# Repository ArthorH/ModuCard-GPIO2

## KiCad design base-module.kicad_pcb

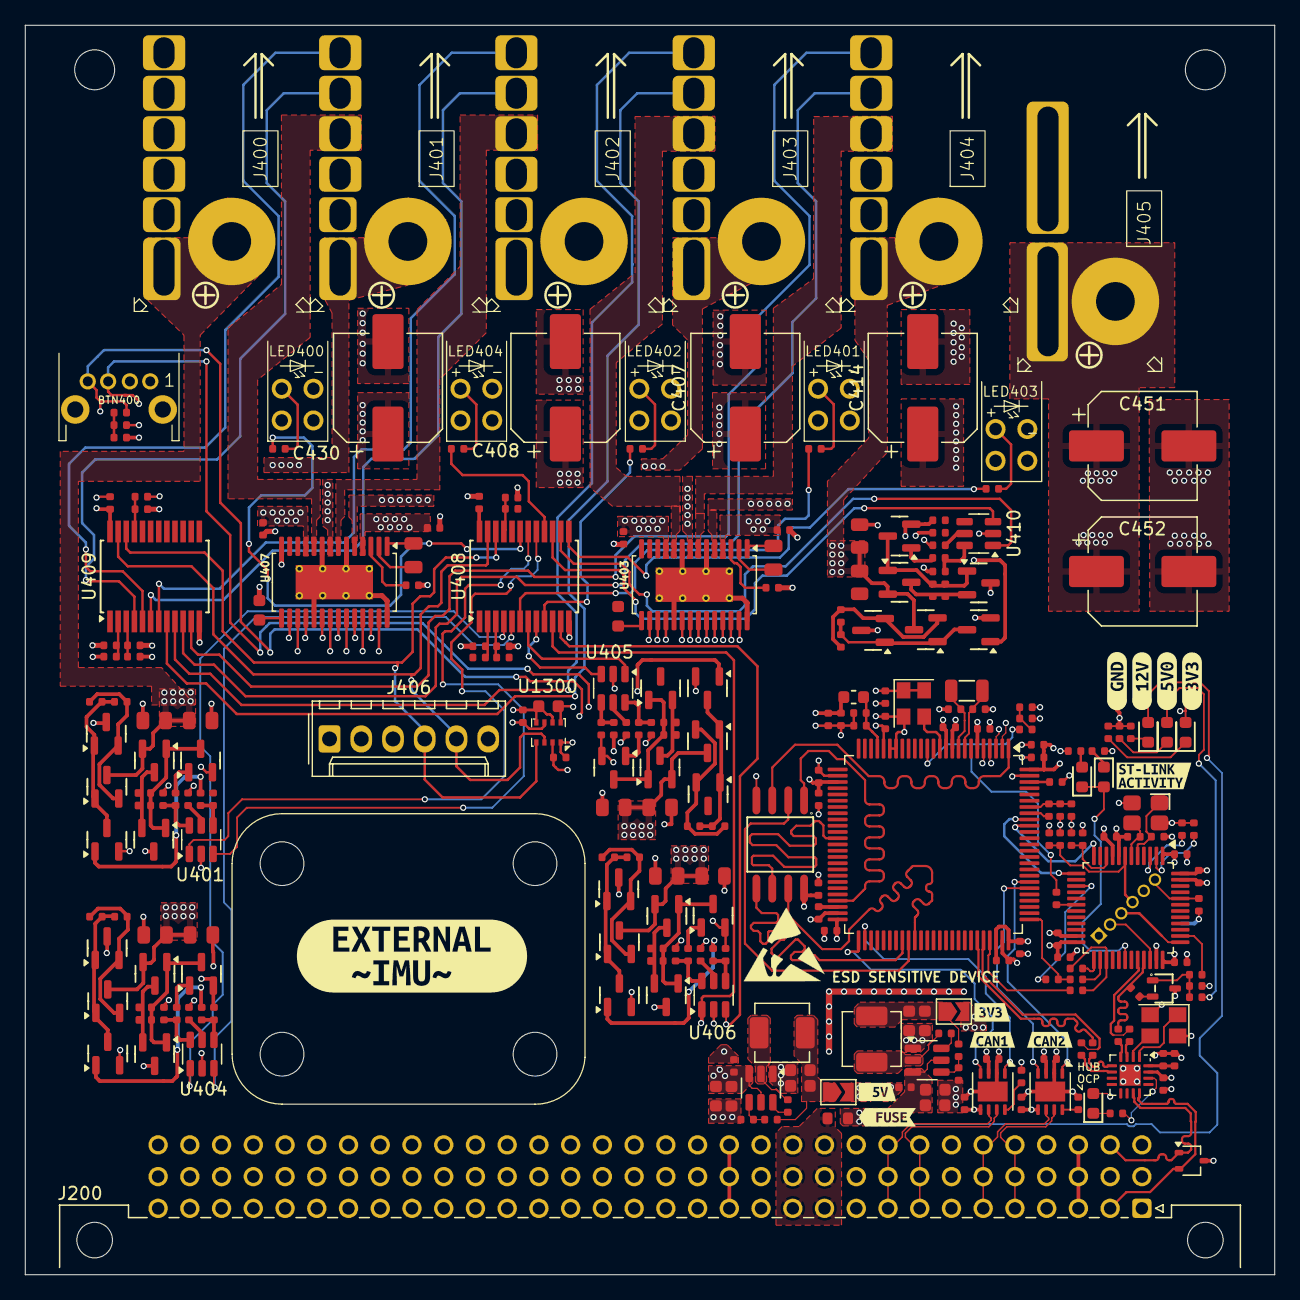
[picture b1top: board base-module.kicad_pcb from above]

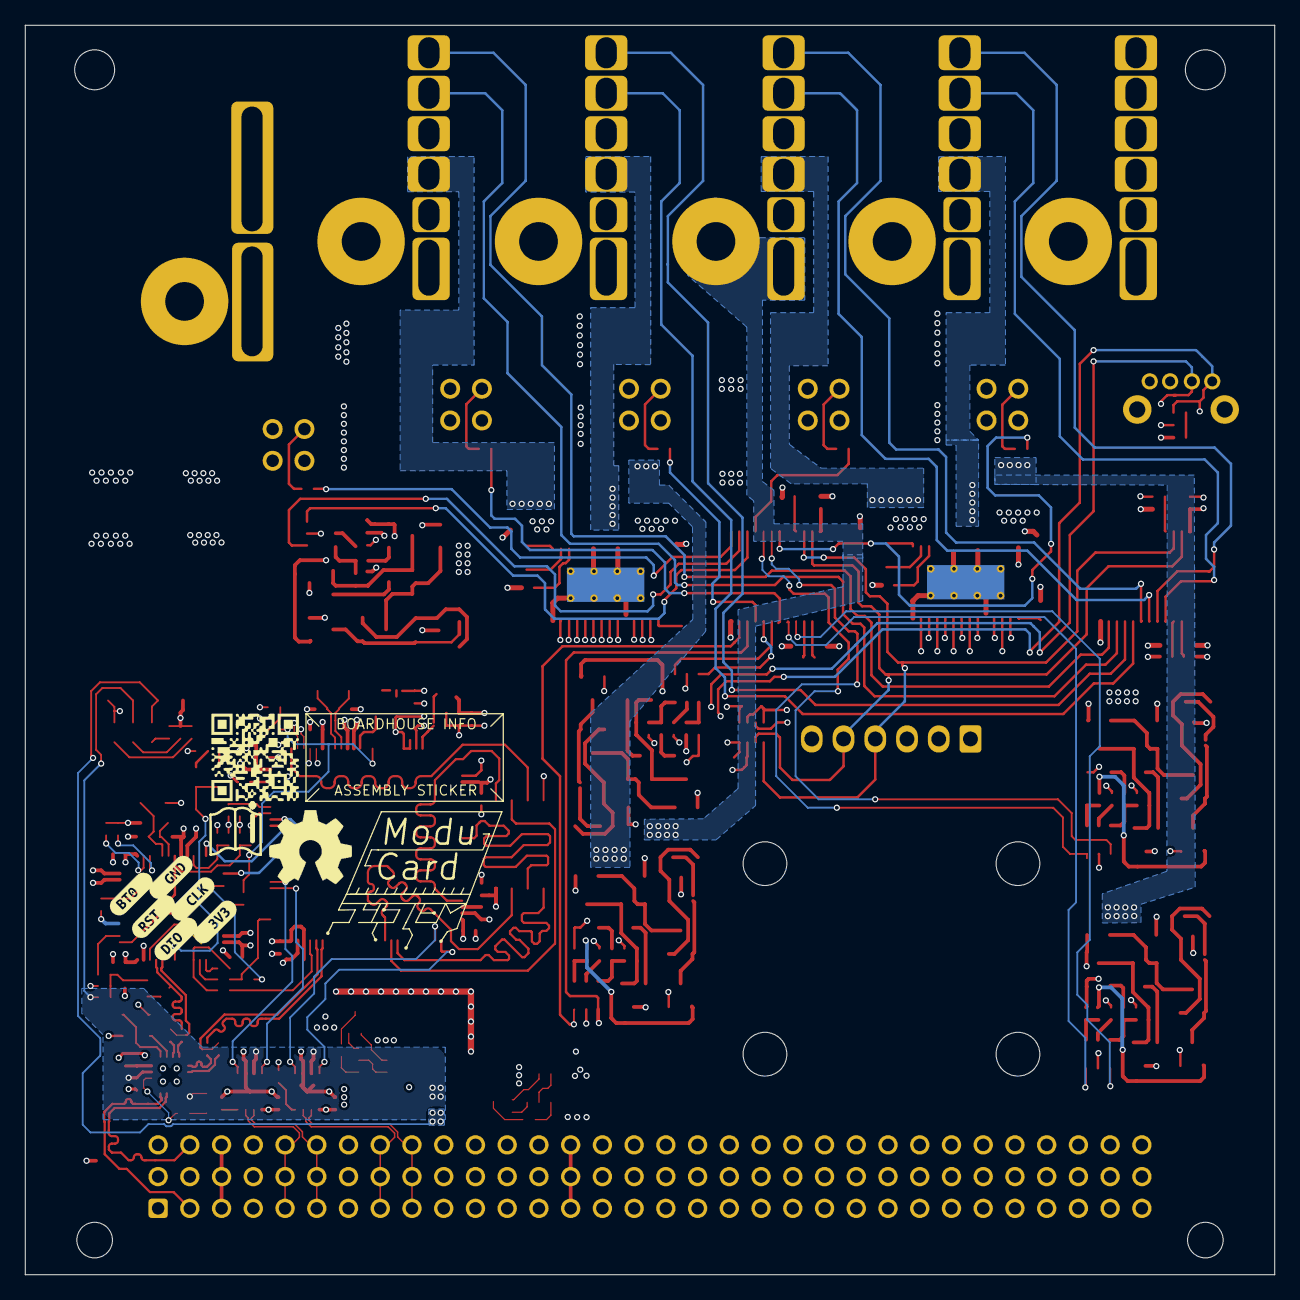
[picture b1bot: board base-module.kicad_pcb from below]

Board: 4 copper layers, 100.0 x 100.0 mm, 287 parts (7 on the bottom side), 183 nets.

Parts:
BTN400: TL2243
C100, C300, C305, C306, C311, C401, C402, C404, C405, C406, C412, C413, C415, C416, C420, C421, C422, C424, C426, C432, C433, C435, C436, C437, C438, C439, C440, C500, C501, C600, C601, C701, C702, C703, C704, C705, C706, C900, C1301, C1302: 100nF; C_0402
C301, C302, C303, C304, C309, C310, C1300: 10uF; C_0603
C307, C308: 22uF; C_0603
C313, C314: 18pF; C_0402
C400, C403, C423, C425, C902: 10uF; C_0402
C407, C408, C414, C430, C451, C452: 47uF; CP_Elec_8x10.5
C409, C411, C429, C431, C700, C904: 1uF; C_0402
C410: 4.7uF; C_0402
C417, C418: 100nF; C_0805
C419, C428: 47nF; C_0603
C427, C434: 2.2uF; C_0402
C441, C442, C443, C444, C445, C446, C447, C448, C449, C450: 10nF; C_0402
C707, C708: 33pF; C_0402
D301, D400, D401, D402, D700, D701: Red; D_0603
F300: 1.5A; R_0603
FB401: FB_0603
H400, H401, H402, H403: MountingHole; MountingHole_3.5mm
J3: Programming header; PinHeader_1x06_P1.27mm_Vertical
J200: 09031967921; DIN41612_R_3x32_Female_Horizontal_THT
J400, J401, J402, J403, J404: Conn_01x06_Socket; Molex-UP-righter
J405: XT60; XT60-RightAngle-Adapter
J406: Adafruit garbage connector; Molex_KK-254_AE-6410-06A_1x06_P2.54mm_Vertical
JP300, JP301: SolderJumper_2_Bridged; SolderJumper-2_P1.3mm_Open_TrianglePad1.0x1.5mm
L300, L301: 3.3uH; L_Changjiang_FXL0420
LED400, LED401, LED402, LED403, LED404: FixLed307
Q400, Q401, Q404, Q405, Q408, Q430, Q431, Q432, Q433, Q434: AO3400A; Q_SOT-23
Q402, Q403, Q406, Q407, Q410, Q411, Q414, Q415, Q418, Q419, Q420, Q421, Q422, Q423, Q424, Q425, Q426, Q427, Q428, Q429: AO3401A; Q_SOT-23
Q700: MMST3904; Q_SOT-323
R300: 54k9; R_0402
R301, R307, R402, R403, R405, R409, R413, R419, R420, R426, R427, R433, R434, R440, R441, R444, R445, R446, R447, R448, R449, R450, R451, R452, R453, R454, R455, R456, R457, R458, R459, R460, R461, R462, R463, R464, R465, R500, R600, R701, R703, R705, R706, R707, R709, R713: 10kΩ; R_0402
R306: 33k2; R_0402
R308, R401, R407, R408, R417, R418, R424, R425, R431, R432, R438, R439: 1kΩ; R_0402
R400, R412, R416, R423, R430, R437: 220Ω; R_0402
R404, R406, R710, R714: 100Ω; R_0402
R410: 2.2kΩ; R_0402
R411: 470Ω; R_0402
R414, R415, R421, R422, R428, R429, R435, R436, R442, R443: 0Ω; R_0805
R700, R702: 100kΩ; R_0402
R704, R708, R715, R716, R900, R901, R902, R903: 22Ω; R_0402
R711: 39kΩ; R_0402
R712: 1.5kΩ; R_0402
TP300, TP301, TP302, TP400: TestPoint; TestPoint_Pad_D1.0mm
U100: W25Q128; SOIC-8_L5.3-W5.3-P1.27-LS8.0-BL
U300, U301: TPS563200; SOT-23-6
U302: CH334P; QFN-16-1EP_3x3mm_P0.5mm_EP1.7x1.7mm
U400: STM32H563VGTx; LQFP-100_14x14mm_P0.5mm
U401, U404, U405, U406, U410: SN74LVC1G19DBVR; SOT-23-6
U402: TPD2E2U06DCK; SOT-323_SC-70
U403, U407: DRV8844PWPR; HTSSOP-28-1EP_4.4x9.7mm_P0.65mm_EP2.75x6.2mm_ThermalVias
U408, U409: TCA9535DBR; SSOP-24_5.3x8.2mm_P0.65mm
U500, U600: TJA1044GTK_3Z; HVSON-8-1EP_3x3mm_P0.65mm_EP1.6x2.4mm
U700: STM32F103CBTx; LQFP-48_7x7mm_P0.5mm
U1300: BMP280; Bosch_LGA-8_2x2.5mm_P0.65mm_ClockwisePinNumbering
X300: Q13FC1350000400; FC-135R_L3.2-W1.5
Y400: ASE-xxxMHz; Oscillator_SMD_Abracon_ASE-4Pin_3.2x2.5mm
Y700: 8 MHz; CRYSTAL-SMD_4P-L3.2-W2.5-BL
Y900: 12Mhz; Crystal_SMD_3225-4Pin_3.2x2.5mm
kibuzzard-67B20BD5: G***; kibuzzard-67B20BD5
kibuzzard-67B63E8D: G***; kibuzzard-67B63E8D
kibuzzard-67B643AC: G***; kibuzzard-67B643AC
kibuzzard-67B643DE: G***; kibuzzard-67B643DE
kibuzzard-67B643EE: G***; kibuzzard-67B643EE
kibuzzard-67B6249A: G***; kibuzzard-67B6249A
kibuzzard-67B6438D: G***; kibuzzard-67B6438D
kibuzzard-67B37005: G***; kibuzzard-67B37005
kibuzzard-67B37418: G***; kibuzzard-67B37418
kibuzzard-67B37472: G***; kibuzzard-67B37472
kibuzzard-67B62451: G***; kibuzzard-67B62451
kibuzzard-67E7D86B: G***; kibuzzard-67E7D86B
kibuzzard-68DC416C: G***; kibuzzard-68DC416C
kibuzzard-68DC4137: G***; kibuzzard-68DC4137
kibuzzard-68DC4152: G***; kibuzzard-68DC4152
kibuzzard-68DC4179: G***; kibuzzard-68DC4179
kibuzzard-6807DF1D: G***; kibuzzard-6807DF1D

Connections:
+3V3: C100.1, C400.1, C401.1, C402.1, C403.1, C404.1, C405.1, C406.1, C420.1, C421.1, C422.1, C425.1, C426.1, C432.1, C433.1, C435.1, C436.1, C437.1, C438.1, C501.1, C601.1, C700.1, C701.1, C702.1, C703.1, C704.1, C705.1, C1300.1, C1301.1, C1302.1, D402.2, FB401.2, J3.1, J406.2, JP301.2 (B), Q700.3 (C), R403.1, R405.1, R700.1, R701.1, R707.1, TP302.1, U100.8 (VCC), U400.6 (VBAT), U400.11 (VDD), U400.21 (VREF+), U400.28 (VDD), U400.50 (VDD), U400.73 (VDDUSB), U400.75 (VDD), U400.100 (VDD), U401.5 (VCC), U404.5 (VCC), U405.5 (VCC), U406.5 (VCC), U410.5 (VCC), U500.5 (VIO), U600.5 (VIO), U700.1 (VBAT), U700.9 (VDDA), U700.24 (VDD), U700.36 (VDD), U700.48 (VDD), U1300.2 (CSB), U1300.6 (VDDIO), U1300.8 (VDD), Y400.1 (EN), Y400.4 (Vdd)
+5V: C439.1, C440.1, C500.2, C600.2, C904.1, D301.2, D401.2, J406.1, JP300.2 (B), Q402.3 (D), Q406.3 (D), Q410.3 (D), Q414.3 (D), Q418.3 (D), R414.1, R421.1, R428.1, R435.1, R442.1, R444.1, R445.1, R446.1, R450.1, R452.1, R456.1, R709.1, TP301.1, U302.15 (5V), U408.24 (VCC), U409.24 (VCC), U500.3 (VCC), U600.3 (VCC)
+5V_STDBY: J200.a3, J200.b3, J200.c3
+12V: F300.1, J200.a11, J200.a12, J200.b11, J200.b12, J200.c11, J200.c12, Q403.3 (D), Q407.3 (D), Q411.3 (D), Q415.3 (D), Q419.3 (D), R415.1, R422.1, R429.1, R436.1, R443.1
+12V_FUSED: C303.1, C304.1, C305.2, C309.1, C310.1, C311.2, D400.2, F300.2, TP300.1, U300.3 (VIN), U300.5 (EN), U301.3 (VIN), U301.5 (EN)
+24V: J200.a14, J200.b14, J200.c14
/Backplane/BACKPLANE.D+: J200.a2, U302.12 (DPU), U402.2
/Backplane/BACKPLANE.D-: J200.c2, U302.11 (DMU), U402.1
/Backplane/CAN1.+: J200.a5, J200.b5, J200.c5, U500.7 (CANH)
/Backplane/CAN1.-: J200.a6, J200.b6, J200.c6, U500.6 (CANL)
/Backplane/CAN2.+: J200.a8, J200.b8, J200.c8, U600.7 (CANH)
/Backplane/CAN2.-: J200.a9, J200.b9, J200.c9, U600.6 (CANL)
/Barometer/BAROMETR_I2C.SCL: J406.4, U408.22 (SCL), U409.22 (SCL), U1300.4 (SCK)
/Barometer/BAROMETR_I2C.SDA: J406.5, U408.23 (SDA), U409.23 (SDA), U1300.3 (SDI)
/CAN transceiver 1/CAN.RX: U400.81 (PD0), U500.4 (RXD)
/CAN transceiver 1/CAN.TX: U400.82 (PD1), U500.1 (TXD)
/CAN transceiver 2/CAN.RX: U400.51 (PB12), U600.4 (RXD)
/CAN transceiver 2/CAN.TX: U400.52 (PB13), U600.1 (TXD)
/GPIO_Conn1/GPIO.Bridge+: J401.3, U407.8 (OUT3)
/GPIO_Conn1/GPIO.Bridge-: J401.4, U407.10 (OUT4)
/GPIO_Conn1/GPIO.EN: U404.3 (~E), U408.5 (P01)
/GPIO_Conn1/GPIO.GPIO1: J401.6, U409.5 (P01)
/GPIO_Conn1/GPIO.GPIO2: J401.5, U409.4 (P00)
/GPIO_Conn1/GPIO.LED: R416.1, U408.6 (P02)
/GPIO_Conn1/GPIO.LV+: J401.1, Q421.3 (D), Q426.2 (S), R421.2, R422.2
/GPIO_Conn1/GPIO.SEL: U404.1 (A), U408.4 (P00)
/GPIO_Conn2/GPIO.Bridge+: J402.3, U407.5 (OUT1)
/GPIO_Conn2/GPIO.Bridge-: J402.4, U407.7 (OUT2)
/GPIO_Conn2/GPIO.EN: U405.3 (~E), U408.8 (P04)
/GPIO_Conn2/GPIO.GPIO1: J402.6, U409.7 (P03)
/GPIO_Conn2/GPIO.GPIO2: J402.5, U409.6 (P02)
/GPIO_Conn2/GPIO.LED: R423.1, U408.9 (P05)
/GPIO_Conn2/GPIO.LV+: J402.1, Q422.3 (D), Q427.2 (S), R428.2, R429.2
/GPIO_Conn2/GPIO.SEL: U405.1 (A), U408.7 (P03)
/GPIO_Conn3/GPIO.Bridge+: J403.3, U403.8 (OUT3)
/GPIO_Conn3/GPIO.Bridge-: J403.4, U403.10 (OUT4)
/GPIO_Conn3/GPIO.EN: U406.3 (~E), U408.11 (P07)
/GPIO_Conn3/GPIO.GPIO1: J403.6, U409.9 (P05)
/GPIO_Conn3/GPIO.GPIO2: J403.5, U409.8 (P04)
/GPIO_Conn3/GPIO.LED: R430.1, U408.13 (P10)
/GPIO_Conn3/GPIO.LV+: J403.1, Q423.3 (D), Q428.2 (S), R435.2, R436.2
/GPIO_Conn3/GPIO.SEL: U406.1 (A), U408.10 (P06)
/GPIO_Conn4/GPIO.Bridge+: J404.3, U403.5 (OUT1)
/GPIO_Conn4/GPIO.Bridge-: J404.4, U403.7 (OUT2)
/GPIO_Conn4/GPIO.EN: U408.15 (P12), U410.3 (~E)
/GPIO_Conn4/GPIO.GPIO1: J404.6, U409.11 (P07)
/GPIO_Conn4/GPIO.GPIO2: J404.5, U409.10 (P06)
/GPIO_Conn4/GPIO.LED: R437.1, U408.16 (P13)
/GPIO_Conn4/GPIO.LV+: J404.1, Q424.3 (D), Q429.2 (S), R442.2, R443.2
/GPIO_Conn4/GPIO.SEL: U408.14 (P11), U410.1 (A)
/GPIO_Conn5/GPIO.EN: U401.3 (~E), U408.18 (P15)
/GPIO_Conn5/GPIO.LED: R400.1, U408.19 (P16)
/GPIO_Conn5/GPIO.LV+: J400.1, Q420.3 (D), Q425.2 (S), R414.2, R415.2
/GPIO_Conn5/GPIO.SEL: U401.1 (A), U408.17 (P14)
/Hbridge1-2/VM: C407.1, C408.1, C409.1, C411.1, C414.1, C429.1, C430.1, C431.1, C451.1, C452.1, J405.1, U403.4 (VM), U403.11 (VM), U407.4 (VM), U407.11 (VM)
/MCU/BOOT0: C410.1, R401.2, R402.1, U400.94 (BOOT0)
/MCU/BOOT_EN: R401.1, U400.93 (PB7)
/MCU/MCU_UART.RX: U400.91 (PB5), U700.12 (PA2)
/MCU/MCU_UART.TX: U400.92 (PB6), U700.13 (PA3)
/MCU/NRST: C415.1, R403.2, R404.1
/MCU/OSC32_IN: C314.1, U400.8 (PC14), X300.2
/MCU/OSC32_OUT: C313.1, U400.9 (PC15), X300.1
/MCU/OSC_IN: U400.12 (PH0), Y400.3 (OUT)
/MCU/QSPI1.CS: U100.1 (CS#), U400.47 (PB10)
/MCU/QSPI1.IO0: U100.5 (DI), U400.58 (PD11)
/MCU/QSPI1.IO1: U100.2 (DO), U400.59 (PD12)
/MCU/QSPI1.IO2: U100.3 (IO2), U400.1 (PE2)
/MCU/QSPI1.IO3: U100.7 (IO3), U400.60 (PD13)
/MCU/QSPI1.SCLK: U100.6 (CLK), U400.37 (PB2)
/MCU/SWD.SWCLK: R704.2, R715.1, U400.76 (PA14(JTCK)
/MCU/SWD.SWDIO: R716.1, U400.72 (PA13(JTMS)
/MCU/SWD.~RST: BTN400.3, R404.2, R708.1, U400.14 (NRST)
/MCU/USB_MCU.D+: R901.1, U400.71 (PA12)
/MCU/USB_MCU.D-: R900.1, U400.70 (PA11)
/MCU/USR_BTN: C416.1, R405.2, R406.1
/MCU/USR_BUTTON: BTN400.4, R406.2, U400.5 (PE6)
/MCU/VCAP_1: C427.1, U400.48 (VCAP)
/MCU/VCAP_2: C434.1, U400.98 (VCAP)
/MCU/VDDA: C423.1, C424.1, FB401.1, U400.22 (VDDA)
/Power/+3V3_UNPROTEC: C307.1, C308.1, JP301.1 (A), L301.2, R306.1
/Power/+5V_UNPROTEC: C301.1, C302.1, JP300.1 (A), L300.2, R300.1
/Power/FB_3V3: R306.2, R307.1, U301.4 (VFB)
/Power/FB_5V0: R300.2, R301.1, U300.4 (VFB)
/Power/SW_3V3: C306.2, L301.1, U301.2 (SW)
/Power/SW_5V0: C300.2, L300.1, U300.2 (SW)
/Power/VBST_3V3: C306.1, U301.6 (VBST)
/Power/VBST_5V0: C300.1, U300.6 (VBST)
/ST-LINK/CLK: J3.3, U700.37 (PA14)
/ST-LINK/DIO: J3.2, U700.34 (PA13)
/ST-LINK/LED: D700.1, D701.2, U700.30 (PA9)
/ST-LINK/ST-LINK.D+: R712.2, R903.1, U700.33 (PA12)
/ST-LINK/ST-LINK.D-: R902.1, U700.32 (PA11)
/ST-LINK/STLINK-BOOT0: J3.6, R702.2, U700.44 (BOOT0)
/ST-LINK/STLINK-OSC_IN: C707.1, U700.5 (PD0), Y700.1
/ST-LINK/STLINK-OSC_OUT: C708.1, U700.6 (PD1), Y700.3
/ST-LINK/STLINK-RST: C706.1, J3.4, R700.2, U700.7 (NRST)
/ST-LINK/USB_RENUM: R710.2, U700.38 (PA15)
/USB-hub/USBOUT1_R.D+: R903.2, U302.4 (DP4)
/USB-hub/USBOUT1_R.D-: R902.2, U302.3 (DM4)
/USB-hub/USB_MCU_R.D+: R901.2, U302.6 (DP3)
/USB-hub/USB_MCU_R.D-: R900.2, U302.5 (DM3)
GND: BTN400.1, BTN400.2, C100.2, C301.2, C302.2, C303.2, C304.2, C305.1, C307.2, C308.2, C309.2, C310.2, C311.1, C313.2, C314.2, C400.2, C401.2, C402.2, C403.2, C404.2, C405.2, C406.2, C407.2, C408.2, C409.2, C410.2, C411.2, C412.1, C413.1, C414.2, C415.2, C416.2, C419.2, C420.2, C421.2, C422.2, C423.2, C424.2, C425.2, C426.2, C427.2, C428.2, C429.2, C430.2, C431.2, C432.2, C433.2, C434.2, C435.2, C436.2, C437.2, C438.2, C439.2, C440.2, C451.2, C452.2, C500.1, C501.2, C600.1, C601.2, C700.2, C701.2, C702.2, C703.2, C704.2, C705.2, C706.2, C707.2, C708.2, C900.2, C902.2, C904.2, C1300.2, C1301.2, C1302.2, J3.5, J200.a1, J200.a4, J200.a7, J200.a10, J200.a13, J200.a15, J200.a32, J200.b1, J200.b2, J200.b4, J200.b7, J200.b10, J200.b13, J200.b15, J200.b32, J200.c1, J200.c4, J200.c7, J200.c10, J200.c13, J200.c15, J200.c32, J400.2, J401.2, J402.2, J403.2, J404.2, J405.2, J406.3, LED400.2, LED401.2, LED402.2, LED403.2, LED404.2, Q400.2 (S), Q401.2 (S), Q404.2 (S), Q405.2 (S), Q408.2 (S), Q430.2 (S), Q431.2 (S), Q432.2 (S), Q433.2 (S), Q434.2 (S), R301.2, R307.2, R402.2, R410.2, R411.2, R412.2, R413.2, R420.2, R427.2, R434.2, R441.2, R447.2, R448.2, R449.2, R451.2, R454.2, R455.2, R461.2, R462.2, R463.2, R464.2, R465.2, R500.2, R600.2, R702.1, R703.2, R705.1, R706.1, R711.2, R713.2, TP400.1, U100.4 (GND), U300.1 (GND), U301.1 (GND), U302.17 (GND), U400.10 (VSS), U400.19 (VSSA), U400.20 (VREF-), U400.27 (VSS), U400.49 (VSS), U400.74 (VSS), U400.99 (VSS), U401.2 (GND), U402.3, U403.6 (SRC12), U403.9 (SRC34), U403.14 (VNEG), U403.19 (LGND), U403.28 (VNEG), U403.29 (PAD), U404.2 (GND), U405.2 (GND), U406.2 (GND), U407.6 (SRC12), U407.9 (SRC34), U407.14 (VNEG), U407.19 (LGND), U407.28 (VNEG), U407.29 (PAD), U408.12 (GND), U409.12 (GND), U410.2 (GND), U500.2 (GND), U500.9 (EP), U600.2 (GND), U600.9 (EP), U700.8 (VSSA), U700.23 (VSS), U700.35 (VSS), U700.47 (VSS), U1300.1 (GND), U1300.5 (SDO), U1300.7 (GND), Y400.2 (GND), Y700.2, Y700.4, Y900.2, Y900.4
unnamed: D301.1, R308.2
unnamed: D400.1, R410.1
unnamed: D401.1, R411.1
unnamed: D402.1, R412.1
unnamed: D700.2, R707.2
unnamed: D701.1, R713.1
unnamed: LED400.1, R400.2
unnamed: LED401.1, R416.2
unnamed: LED402.1, R423.2
unnamed: LED403.1, R430.2
unnamed: LED404.1, R437.2
unnamed: C446.1, Q400.3 (D), Q403.1 (G), Q420.1 (G), R453.1
unnamed: Q400.1 (G), R408.2
unnamed: C447.1, Q401.3 (D), Q407.1 (G), Q421.1 (G), R457.1
unnamed: Q401.1 (G), R418.2
unnamed: C441.1, Q402.1 (G), Q425.1 (G), Q430.3 (D), R409.1
unnamed: C441.2, Q402.2 (S), Q425.3 (D), R409.2
unnamed: C446.2, Q403.2 (S), Q420.2 (S), R453.2
unnamed: C448.1, Q404.3 (D), Q411.1 (G), Q422.1 (G), R458.1
unnamed: Q404.1 (G), R425.2
unnamed: C449.1, Q405.3 (D), Q415.1 (G), Q423.1 (G), R459.1
unnamed: Q405.1 (G), R432.2
unnamed: C442.1, Q406.1 (G), Q426.1 (G), Q431.3 (D), R419.1
unnamed: C442.2, Q406.2 (S), Q426.3 (D), R419.2
unnamed: C447.2, Q407.2 (S), Q421.2 (S), R457.2
unnamed: C450.1, Q408.3 (D), Q419.1 (G), Q424.1 (G), R460.1
unnamed: Q408.1 (G), R439.2
unnamed: C443.1, Q410.1 (G), Q427.1 (G), Q432.3 (D), R426.1
unnamed: C443.2, Q410.2 (S), Q427.3 (D), R426.2
unnamed: C448.2, Q411.2 (S), Q422.2 (S), R458.2
unnamed: C444.1, Q414.1 (G), Q428.1 (G), Q433.3 (D), R433.1
unnamed: C444.2, Q414.2 (S), Q428.3 (D), R433.2
unnamed: C449.2, Q415.2 (S), Q423.2 (S), R459.2
unnamed: C445.1, Q418.1 (G), Q429.1 (G), Q434.3 (D), R440.1
unnamed: C445.2, Q418.2 (S), Q429.3 (D), R440.2
unnamed: C450.2, Q419.2 (S), Q424.2 (S), R460.2
unnamed: Q430.1 (G), R407.2
unnamed: Q431.1 (G), R417.2
unnamed: Q432.1 (G), R424.2
unnamed: Q433.1 (G), R431.2
unnamed: Q434.1 (G), R438.2
unnamed: Q700.1 (B), R709.2, R710.1, R711.1
unnamed: Q700.2 (E), R712.1
unnamed: C900.1, C902.1, U302.16 (3V3)
unnamed: R308.1, U302.14 (PGANG)
unnamed: U302.2 (XI), Y900.3
unnamed: U302.1 (XO), Y900.1
unnamed: R407.1, R413.1, U401.6 (Y0)
unnamed: R408.1, R461.1, U401.4 (Y1)
unnamed: C417.2, U403.1 (CP1)
unnamed: C417.1, U403.2 (CP2)
unnamed: C419.1, U403.15 (V3P3OUT)
unnamed: C413.2, U403.3 (VCP)
unnamed: R417.1, R420.1, U404.6 (Y0)
unnamed: R418.1, R462.1, U404.4 (Y1)
unnamed: R424.1, R427.1, U405.6 (Y0)
unnamed: R425.1, R463.1, U405.4 (Y1)
unnamed: R431.1, R434.1, U406.6 (Y0)
unnamed: R432.1, R464.1, U406.4 (Y1)
unnamed: C418.2, U407.1 (CP1)
unnamed: C418.1, U407.2 (CP2)
unnamed: C428.1, U407.15 (V3P3OUT)
unnamed: C412.2, U407.3 (VCP)
unnamed: R446.2, R449.1, U408.21 (A0)
unnamed: R445.2, R448.1, U408.2 (A1)
unnamed: R444.2, R447.1, U408.3 (A2)
unnamed: R454.1, R456.2, U409.21 (A0)
unnamed: R452.2, R455.1, U409.2 (A1)
unnamed: R450.2, R451.1, U409.3 (A2)
unnamed: R438.1, R441.1, U410.6 (Y0)
unnamed: R439.1, R465.1, U410.4 (Y1)
unnamed: R500.1, U500.8 (STB)
unnamed: R600.1, U600.8 (STB)
unnamed: R701.2, R703.1, U700.10 (PA0)
unnamed: R704.1, U700.15 (PA5)
unnamed: R708.2, U700.18 (PB0)
unnamed: R714.2, U700.25 (PB12)
unnamed: R715.2, U700.26 (PB13)
unnamed: R714.1, R716.2, U700.27 (PB14)
unnamed: R705.2, U700.2 (PC13)
unnamed: R706.2, U700.3 (PC14)

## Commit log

2025-11-13 schematic
2025-11-18 layout go brrr
2025-11-20 layouting
2025-11-20 layoutig
